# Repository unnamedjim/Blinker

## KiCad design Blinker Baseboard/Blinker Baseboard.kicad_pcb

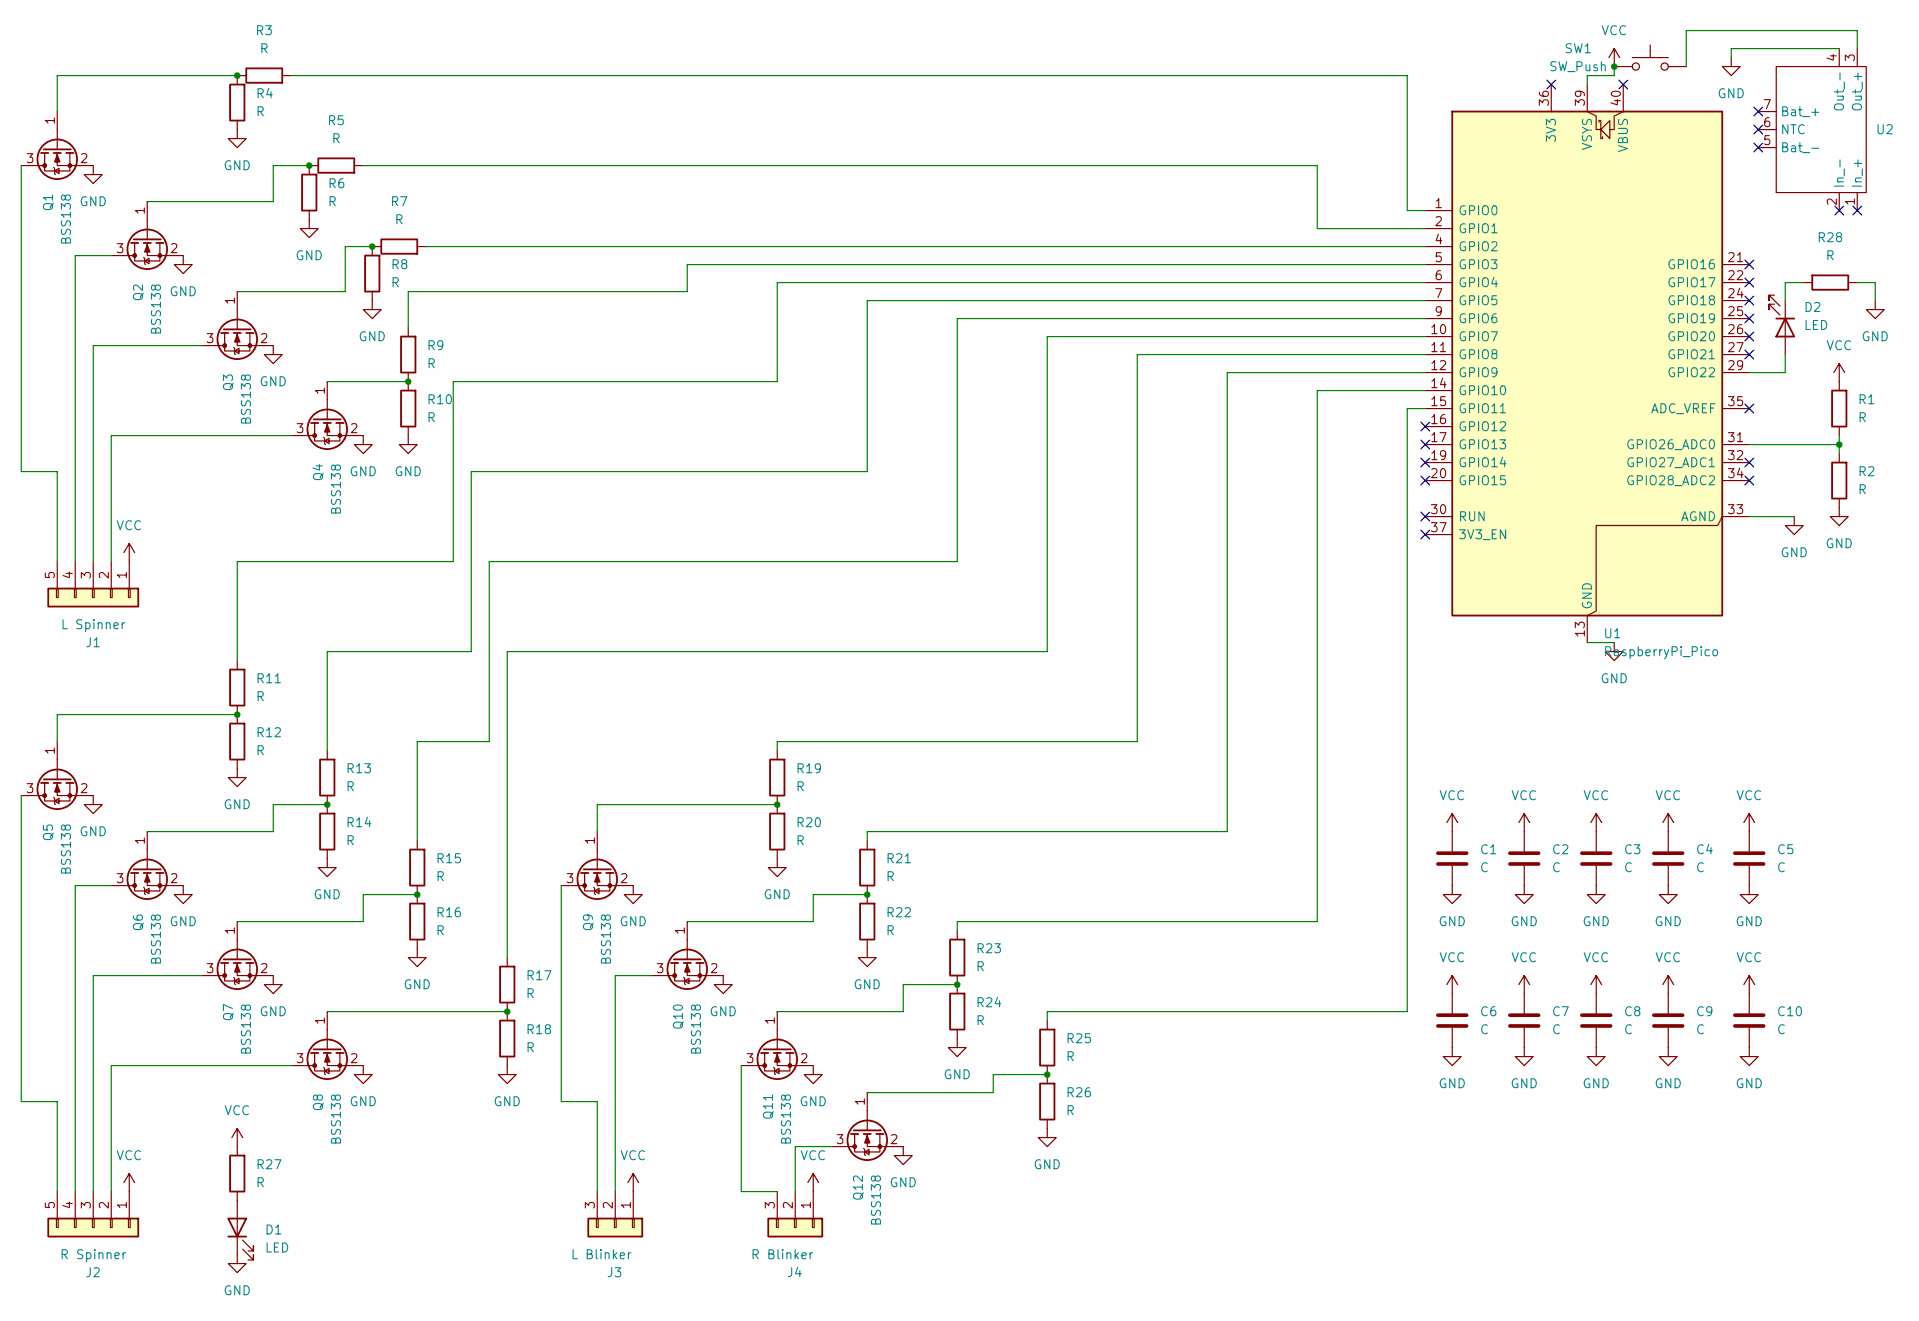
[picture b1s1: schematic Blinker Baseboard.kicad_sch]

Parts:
C1, C2, C3, C4, C5, C6, C7, C8, C9, C10: C; C_0805_2012Metric_Pad1.18x1.45mm_HandSolder
D1, D2: LED; LED_0805_2012Metric_Pad1.15x1.40mm_HandSolder
J1: L Spinner; PinHeader_1x05_P2.54mm_Vertical
J2: R Spinner; PinHeader_1x05_P2.54mm_Vertical
J3: L Blinker; PinHeader_1x03_P2.54mm_Vertical
J4: R Blinker; PinHeader_1x03_P2.54mm_Vertical
Q1, Q2, Q3, Q4, Q5, Q6, Q7, Q8, Q9, Q10, Q11, Q12: BSS138; SOT-23
R1, R2, R3, R4, R5, R6, R7, R8, R9, R10, R11, R12, R13, R14, R15, R16, R17, R18, R19, R20, R21, R22, R23, R24, R25, R26, R27, R28: R; R_0805_2012Metric_Pad1.20x1.40mm_HandSolder
SW1: SW_Push; PinHeader_1x02_P2.54mm_Vertical
U1: RaspberryPi_Pico; RaspberryPi_Pico_Common
U2: Electrokit LiPo charger

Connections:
GND: C1.2, C2.2, C3.2, C4.2, C5.2, C6.2, C7.2, C8.2, C9.2, C10.2, D1.1 (K), Q1.2 (S), Q2.2 (S), Q3.2 (S), Q4.2 (S), Q5.2 (S), Q6.2 (S), Q7.2 (S), Q8.2 (S), Q9.2 (S), Q10.2 (S), Q11.2 (S), Q12.2 (S), R2.1, R4.1, R6.1, R8.1, R10.1, R12.1, R14.1, R16.1, R18.1, R20.1, R22.1, R24.1, R26.1, R28.1, U1.3 (GND), U1.8 (GND), U1.13 (GND), U1.18 (GND), U1.23 (GND), U1.28 (GND), U1.33 (AGND), U1.38 (GND), U2.4 (Out_-)
unnamed: D1.2 (A), R27.1
unnamed: D2.2 (A), U1.29 (GPIO22)
unnamed: D2.1 (K), R28.2
unnamed: J1.2, Q4.3 (D)
unnamed: J1.3, Q3.3 (D)
unnamed: J1.4, Q2.3 (D)
unnamed: J1.5, Q1.3 (D)
unnamed: J2.2, Q8.3 (D)
unnamed: J2.3, Q7.3 (D)
unnamed: J2.4, Q6.3 (D)
unnamed: J2.5, Q5.3 (D)
unnamed: J3.2, Q10.3 (D)
unnamed: J3.3, Q9.3 (D)
unnamed: J4.2, Q12.3 (D)
unnamed: J4.3, Q11.3 (D)
unnamed: Q1.1 (G), R3.1, R4.2
unnamed: Q2.1 (G), R5.1, R6.2
unnamed: Q3.1 (G), R7.1, R8.2
unnamed: Q4.1 (G), R9.1, R10.2
unnamed: Q5.1 (G), R11.1, R12.2
unnamed: Q6.1 (G), R13.1, R14.2
unnamed: Q7.1 (G), R15.1, R16.2
unnamed: Q8.1 (G), R17.1, R18.2
unnamed: Q9.1 (G), R19.1, R20.2
unnamed: Q10.1 (G), R21.1, R22.2
unnamed: Q11.1 (G), R23.1, R24.2
unnamed: Q12.1 (G), R25.1, R26.2
unnamed: R3.2, U1.1 (GPIO0)
unnamed: R5.2, U1.2 (GPIO1)
unnamed: R7.2, U1.4 (GPIO2)
unnamed: R9.2, U1.5 (GPIO3)
unnamed: R11.2, U1.6 (GPIO4)
unnamed: R13.2, U1.7 (GPIO5)
unnamed: R15.2, U1.9 (GPIO6)
unnamed: R17.2, U1.10 (GPIO7)
unnamed: R19.2, U1.11 (GPIO8)
unnamed: R21.2, U1.12 (GPIO9)
unnamed: R23.2, U1.14 (GPIO10)
unnamed: R25.2, U1.15 (GPIO11)
unnamed: R1.1, R2.2, U1.31 (GPIO26_ADC0)
unnamed: SW1.2, U2.3 (Out_+)
VCC: C1.1, C2.1, C3.1, C4.1, C5.1, C6.1, C7.1, C8.1, C9.1, C10.1, J1.1, J2.1, J3.1, J4.1, R1.2, R27.2, SW1.1, U1.39 (VSYS)

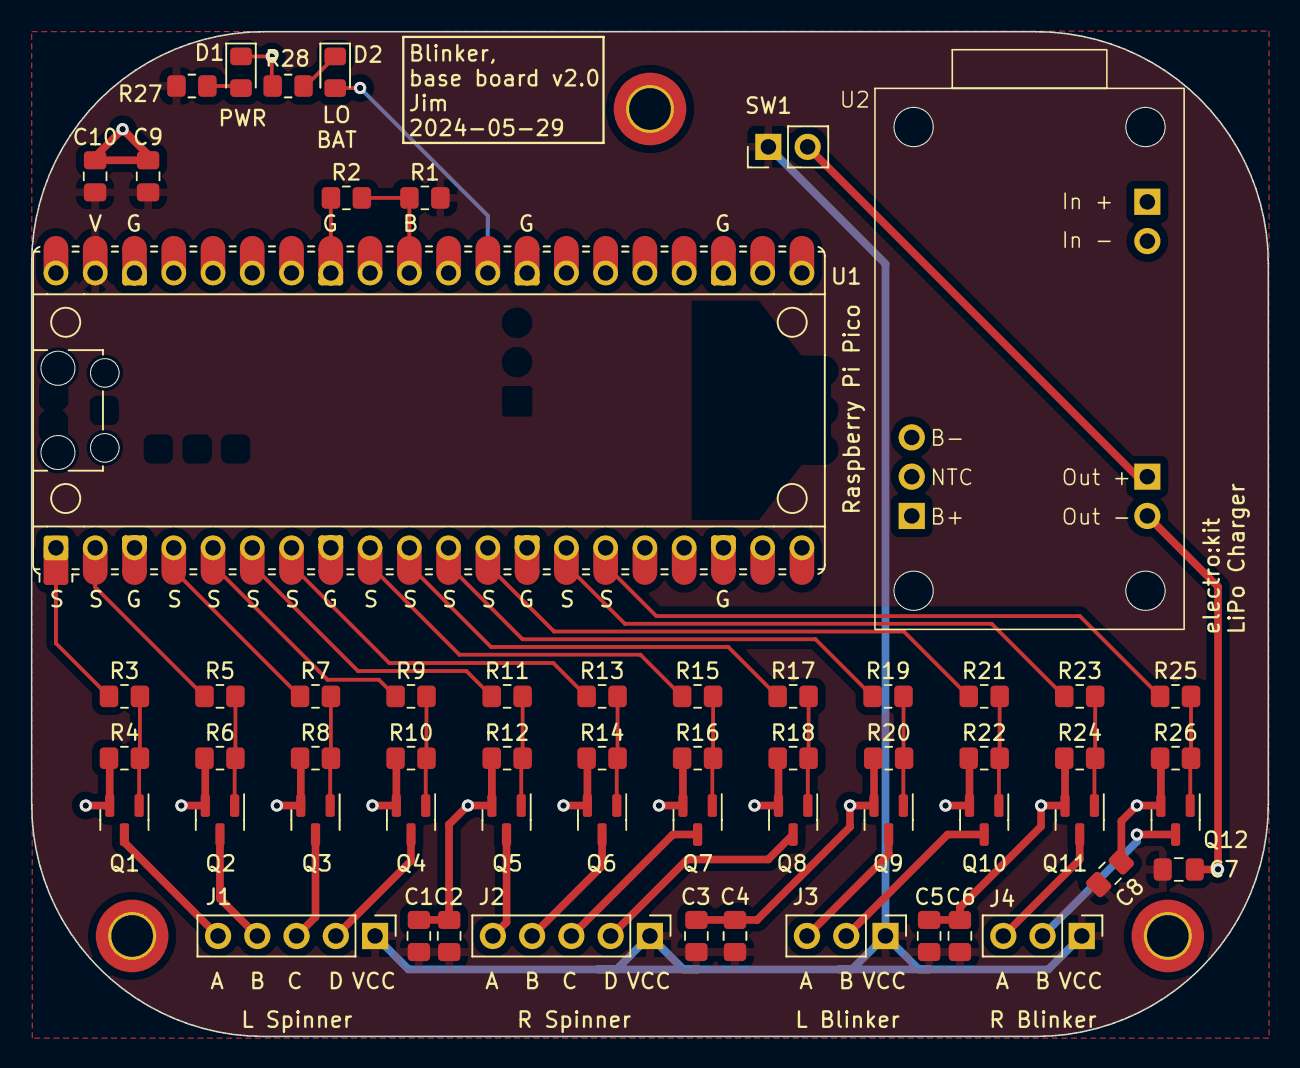
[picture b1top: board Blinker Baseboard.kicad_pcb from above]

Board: 2 copper layers, 80.0 x 65.0 mm, 59 parts (0 on the bottom side), 43 nets.

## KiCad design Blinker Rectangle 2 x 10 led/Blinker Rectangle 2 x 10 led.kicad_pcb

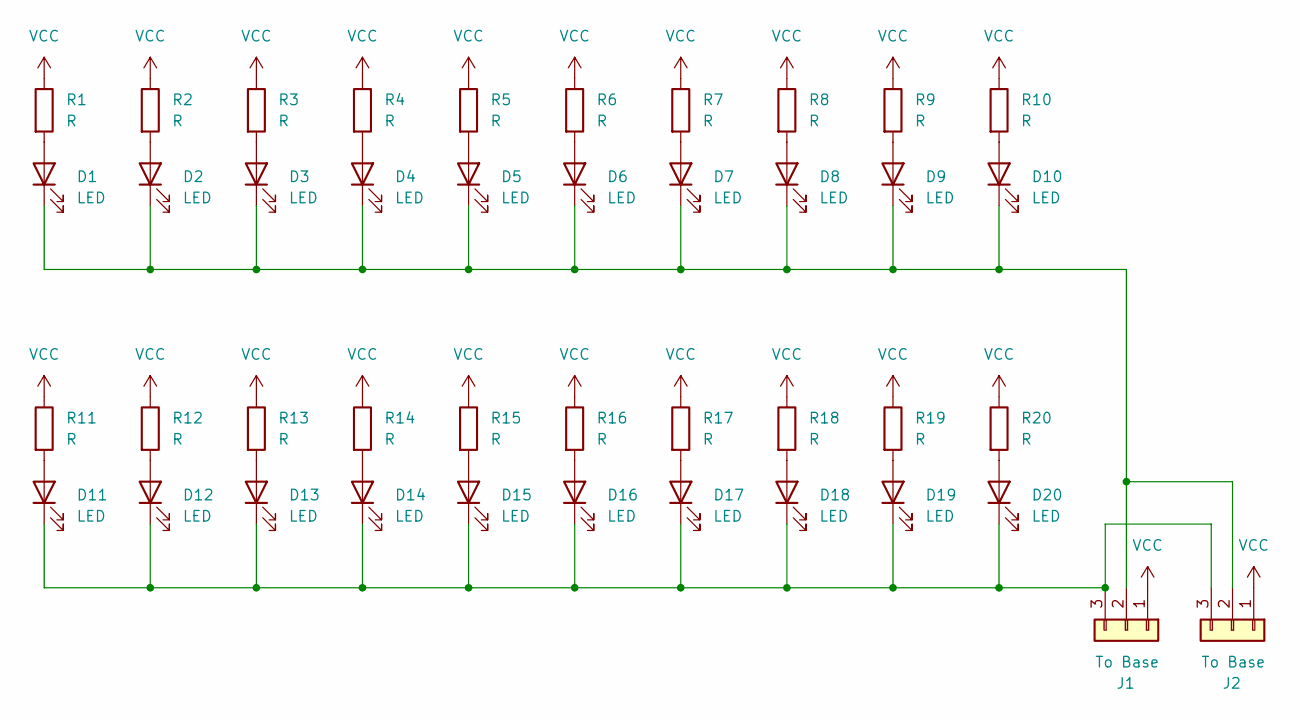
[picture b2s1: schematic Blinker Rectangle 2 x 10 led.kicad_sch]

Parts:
D1, D2, D3, D4, D5, D6, D7, D8, D9, D10, D11, D12, D13, D14, D15, D16, D17, D18, D19, D20: LED; D_1206_3216Metric_Pad1.42x1.75mm_HandSolder
J1, J2: To Base; PinHeader_1x03_P2.54mm_Vertical
R1, R2, R3, R4, R5, R6, R7, R8, R9, R10, R11, R12, R13, R14, R15, R16, R17, R18, R19, R20: R; R_1206_3216Metric_Pad1.30x1.75mm_HandSolder

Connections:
unnamed: D1.2 (A), R1.2
unnamed: D1.1 (K), D2.1 (K), D3.1 (K), D4.1 (K), D5.1 (K), D6.1 (K), D7.1 (K), D8.1 (K), D9.1 (K), D10.1 (K), J1.2, J2.2
unnamed: D2.2 (A), R2.2
unnamed: D3.2 (A), R3.2
unnamed: D4.2 (A), R4.2
unnamed: D5.2 (A), R5.2
unnamed: D6.2 (A), R6.2
unnamed: D7.2 (A), R7.2
unnamed: D8.2 (A), R8.2
unnamed: D9.2 (A), R9.2
unnamed: D10.2 (A), R10.2
unnamed: D11.2 (A), R11.2
unnamed: D11.1 (K), D12.1 (K), D13.1 (K), D14.1 (K), D15.1 (K), D16.1 (K), D17.1 (K), D18.1 (K), D19.1 (K), D20.1 (K), J1.3, J2.3
unnamed: D12.2 (A), R12.2
unnamed: D13.2 (A), R13.2
unnamed: D14.2 (A), R14.2
unnamed: D15.2 (A), R15.2
unnamed: D16.2 (A), R16.2
unnamed: D17.2 (A), R17.2
unnamed: D18.2 (A), R18.2
unnamed: D19.2 (A), R19.2
unnamed: D20.2 (A), R20.2
VCC: J1.1, J2.1, R1.1, R2.1, R3.1, R4.1, R5.1, R6.1, R7.1, R8.1, R9.1, R10.1, R11.1, R12.1, R13.1, R14.1, R15.1, R16.1, R17.1, R18.1, R19.1, R20.1

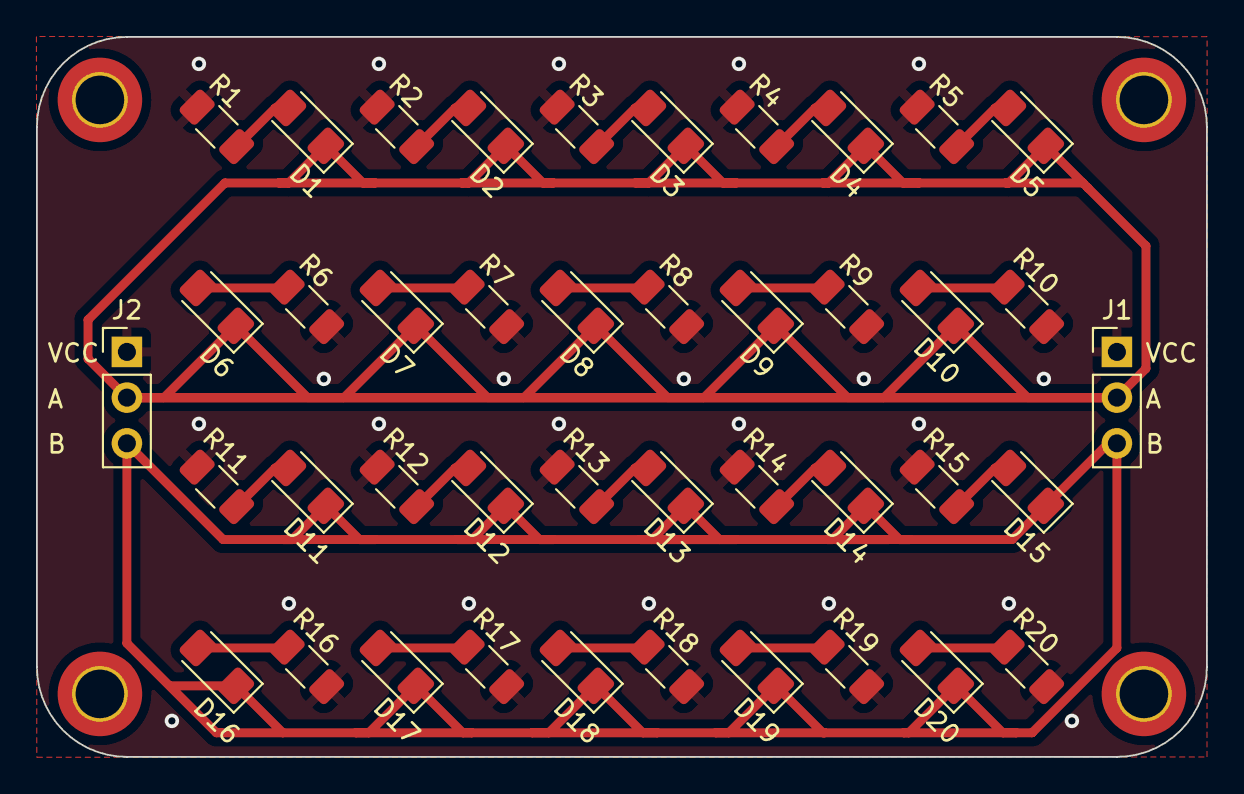
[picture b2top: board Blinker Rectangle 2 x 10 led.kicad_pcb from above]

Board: 2 copper layers, 65.0 x 40.0 mm, 42 parts (0 on the bottom side), 23 nets.

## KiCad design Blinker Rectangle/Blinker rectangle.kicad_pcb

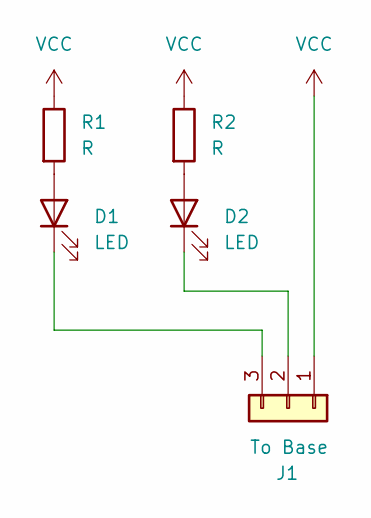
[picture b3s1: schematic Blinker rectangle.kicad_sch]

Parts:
D1, D2: LED; LED_1210_3225Metric
J1: To Base; Molex_PicoBlade_53047-0310_1x03_P1.25mm_Vertical
R1, R2: R; R_1206_3216Metric

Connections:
unnamed: D1.2 (A), R1.2
unnamed: D1.1 (K), J1.3
unnamed: D2.2 (A), R2.2
unnamed: D2.1 (K), J1.2
VCC: J1.1, R1.1, R2.1

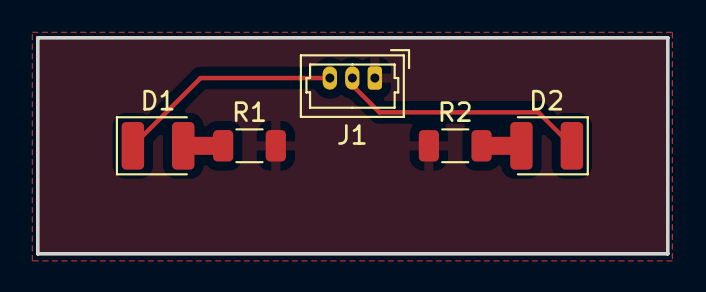
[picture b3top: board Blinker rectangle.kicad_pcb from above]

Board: 2 copper layers, 35.0 x 12.0 mm, 5 parts (0 on the bottom side), 5 nets.

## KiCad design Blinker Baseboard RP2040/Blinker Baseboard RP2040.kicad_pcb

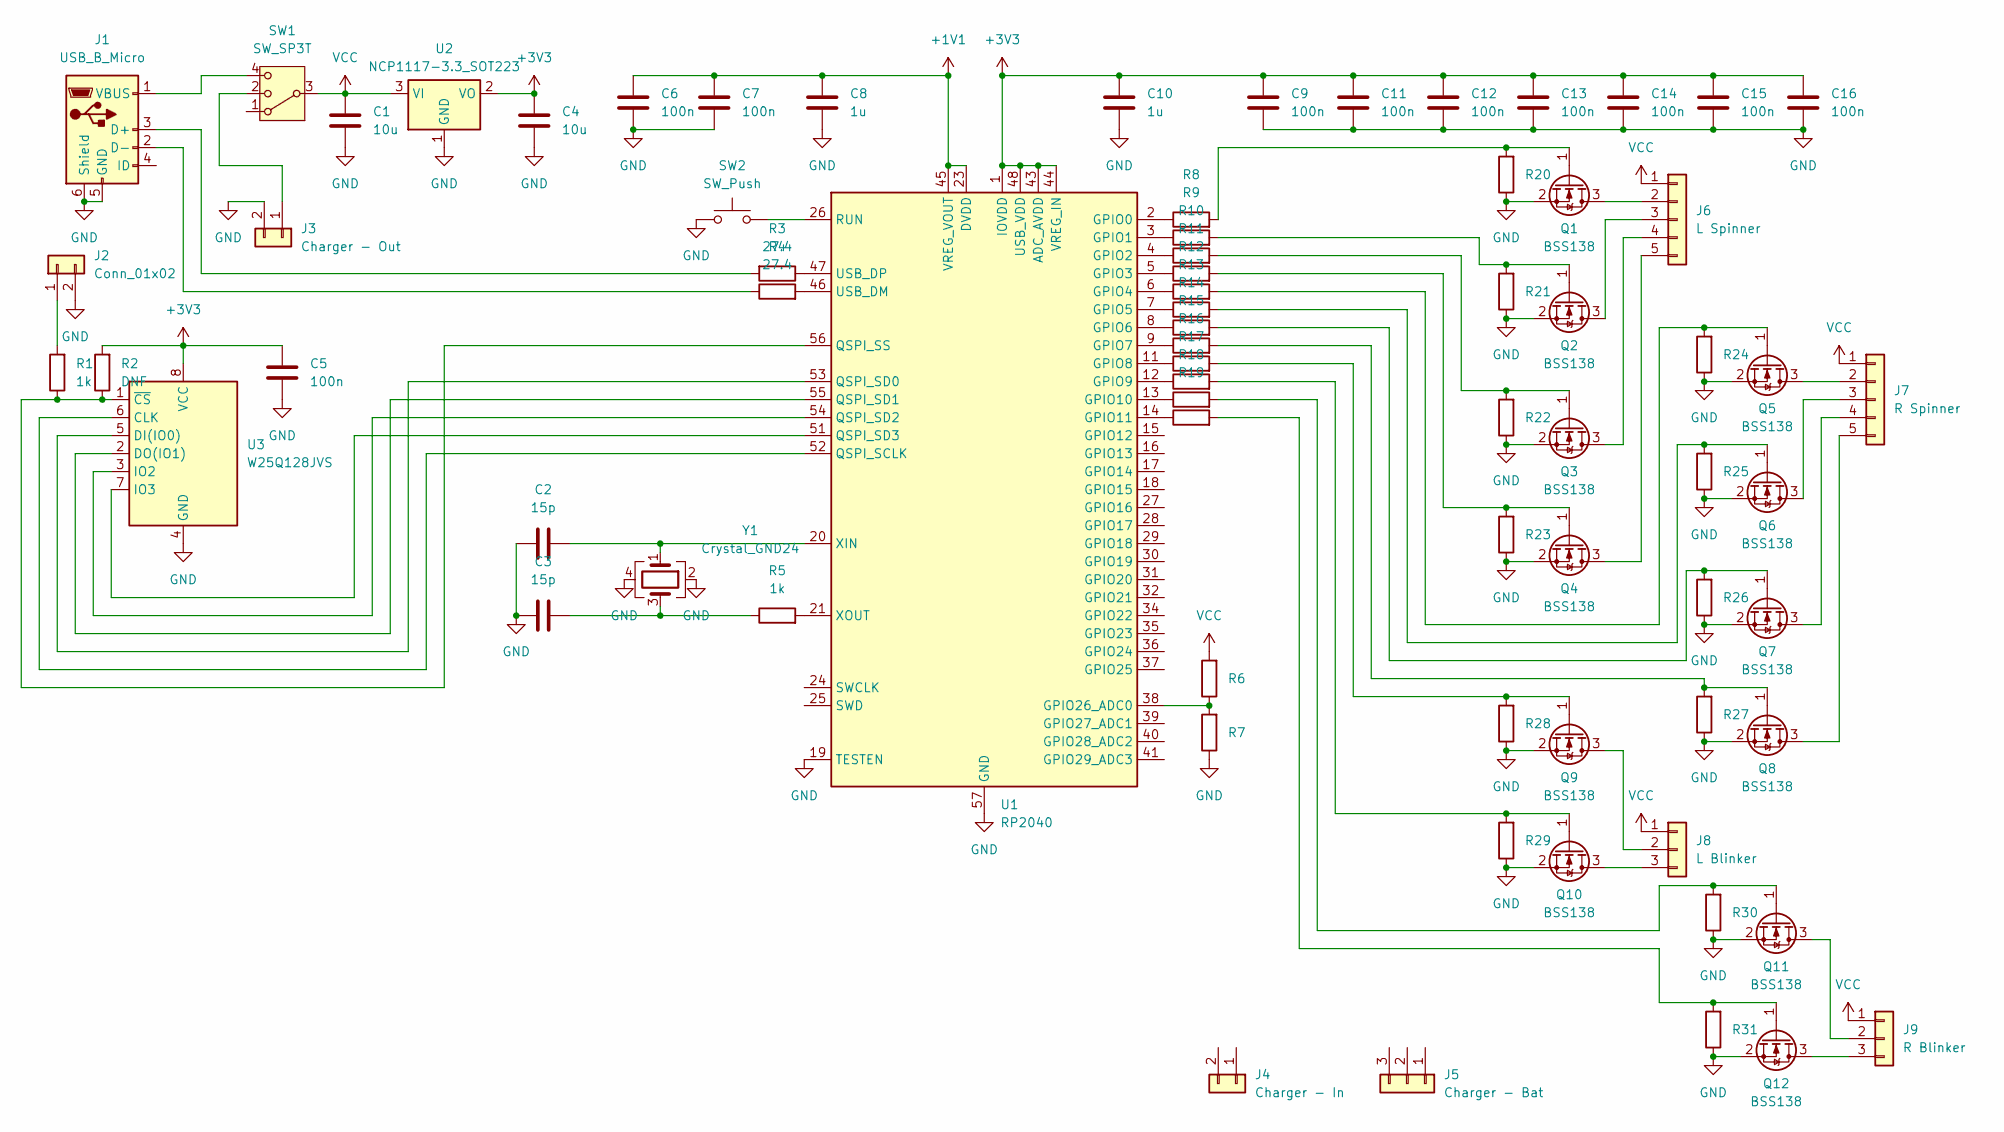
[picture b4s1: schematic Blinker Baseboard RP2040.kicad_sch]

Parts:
C1, C4: 10u; C_0805_2012Metric
C2, C3: 15p; C_0805_2012Metric
C5, C6, C7, C9, C11, C12, C13, C14, C15, C16: 100n; C_0805_2012Metric
C8, C10: 1u; C_0805_2012Metric
J1: USB_B_Micro; USB_Micro-B_Amphenol_10104110_Horizontal
J2: Conn_01x02; PinHeader_1x02_P2.54mm_Vertical
J3: Charger - Out; PinHeader_1x02_P2.54mm_Vertical
J4: Charger - In; PinHeader_1x02_P2.54mm_Vertical
J5: Charger - Bat; PinHeader_1x03_P2.54mm_Vertical
J6: L Spinner; Molex_PicoBlade_53047-0510_1x05_P1.25mm_Vertical
J7: R Spinner; Molex_PicoBlade_53047-0510_1x05_P1.25mm_Vertical
J8: L Blinker; Molex_PicoBlade_53047-0310_1x03_P1.25mm_Vertical
J9: R Blinker; Molex_PicoBlade_53047-0310_1x03_P1.25mm_Vertical
Q1, Q2, Q3, Q4, Q5, Q6, Q7, Q8, Q9, Q10, Q11, Q12: BSS138; SOT-23
R1, R5: 1k; R_0805_2012Metric
R2: DNF; R_0805_2012Metric
R3, R4: 27.4; R_0805_2012Metric
R6, R7, R8, R9, R10, R11, R12, R13, R14, R15, R16, R17, R18, R19, R20, R21, R22, R23, R24, R25, R26, R27, R28, R29, R30, R31: R_0805_2012Metric
SW1: SW_SP3T; Molex_PicoBlade_53047-0410_1x04_P1.25mm_Vertical
SW2: SW_Push; Molex_PicoBlade_53047-0210_1x02_P1.25mm_Vertical
U1: RP2040; QFN-56-1EP_7x7mm_P0.4mm_EP3.2x3.2mm
U2: NCP1117-3.3_SOT223; SOT-223-3_TabPin2
U3: W25Q128JVS; SOIC-8_5.23x5.23mm_P1.27mm
Y1: Crystal_GND24; Crystal_SMD_3225-4Pin_3.2x2.5mm

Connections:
+1V1: C6.1, C7.1, C8.1, U1.23 (DVDD), U1.45 (VREG_VOUT), U1.50 (DVDD)
+3V3: C4.1, C5.1, C9.1, C10.1, C11.1, C12.1, C13.1, C14.1, C15.1, C16.1, R2.2, U1.1 (IOVDD), U1.10 (IOVDD), U1.22 (IOVDD), U1.33 (IOVDD), U1.42 (IOVDD), U1.43 (ADC_AVDD), U1.44 (VREG_IN), U1.48 (USB_VDD), U1.49 (IOVDD), U2.2 (VO), U3.8 (VCC)
GND: C1.2, C2.1, C3.1, C4.2, C5.2, C6.2, C7.2, C8.2, C9.2, C10.2, C11.2, C12.2, C13.2, C14.2, C15.2, C16.2, J1.5 (GND), J1.6 (Shield), J2.2, J3.2, Q1.2 (S), Q2.2 (S), Q3.2 (S), Q4.2 (S), Q5.2 (S), Q6.2 (S), Q7.2 (S), Q8.2 (S), Q9.2 (S), Q10.2 (S), Q11.2 (S), Q12.2 (S), R7.1, R20.1, R21.1, R22.1, R23.1, R24.1, R25.1, R26.1, R27.1, R28.1, R29.1, R30.1, R31.1, SW2.1, U1.19 (TESTEN), U1.57 (GND), U2.1 (GND), U3.4 (GND), Y1.2, Y1.4
unnamed: C3.2, R5.1, Y1.3
unnamed: J1.3 (D+), R3.2
unnamed: J1.2 (D-), R4.1
unnamed: J1.1 (VBUS), SW1.4
unnamed: J2.1, R1.2
unnamed: J3.1, SW1.2
unnamed: J6.2, Q1.3 (D)
unnamed: J6.3, Q2.3 (D)
unnamed: J6.4, Q3.3 (D)
unnamed: J6.5, Q4.3 (D)
unnamed: J7.2, Q5.3 (D)
unnamed: J7.3, Q6.3 (D)
unnamed: J7.4, Q7.3 (D)
unnamed: J7.5, Q8.3 (D)
unnamed: J8.2, Q9.3 (D)
unnamed: J8.3, Q10.3 (D)
unnamed: J9.2, Q11.3 (D)
unnamed: J9.3, Q12.3 (D)
unnamed: Q1.1 (G), R8.2, R20.2
unnamed: Q2.1 (G), R9.2, R21.2
unnamed: Q3.1 (G), R10.2, R22.2
unnamed: Q4.1 (G), R11.2, R23.2
unnamed: Q5.1 (G), R12.2, R24.2
unnamed: Q6.1 (G), R13.2, R25.2
unnamed: Q7.1 (G), R14.2, R26.2
unnamed: Q8.1 (G), R15.2, R27.2
unnamed: Q9.1 (G), R16.2, R28.2
unnamed: Q10.1 (G), R17.2, R29.2
unnamed: Q11.1 (G), R18.2, R30.2
unnamed: Q12.1 (G), R19.2, R31.2
unnamed: R8.1, U1.2 (GPIO0)
unnamed: R9.1, U1.3 (GPIO1)
unnamed: R10.1, U1.4 (GPIO2)
unnamed: R11.1, U1.5 (GPIO3)
unnamed: R12.1, U1.6 (GPIO4)
unnamed: R13.1, U1.7 (GPIO5)
unnamed: R14.1, U1.8 (GPIO6)
unnamed: R15.1, U1.9 (GPIO7)
unnamed: R16.1, U1.11 (GPIO8)
unnamed: R17.1, U1.12 (GPIO9)
unnamed: R18.1, U1.13 (GPIO10)
unnamed: R19.1, U1.14 (GPIO11)
unnamed: R6.1, R7.2, U1.38 (GPIO26_ADC0)
unnamed: U1.52 (QSPI_SCLK), U3.6 (CLK)
unnamed: U1.53 (QSPI_SD0), U3.5 (DI(IO0))
unnamed: U1.55 (QSPI_SD1), U3.2 (DO(IO1))
unnamed: U1.54 (QSPI_SD2), U3.3 (IO2)
unnamed: U1.51 (QSPI_SD3), U3.7 (IO3)
unnamed: R1.1, R2.1, U1.56 (QSPI_SS), U3.1 (~CS)
unnamed: SW2.2, U1.26 (RUN)
unnamed: R4.2, U1.46 (USB_DM)
unnamed: R3.1, U1.47 (USB_DP)
unnamed: C2.2, U1.20 (XIN), Y1.1
unnamed: R5.2, U1.21 (XOUT)
VCC: C1.1, J6.1, J7.1, J8.1, J9.1, R6.2, SW1.3, U2.3 (VI)

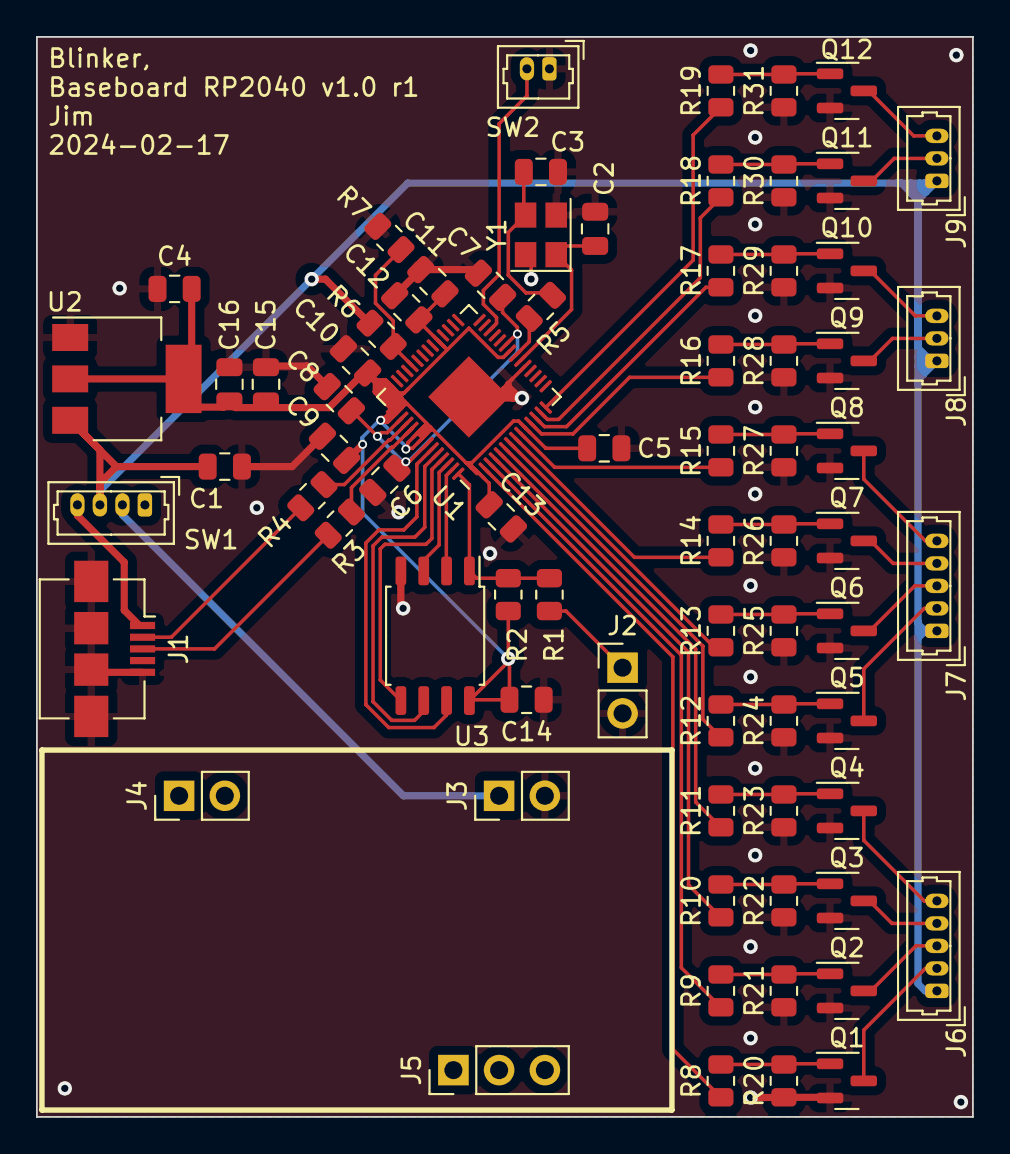
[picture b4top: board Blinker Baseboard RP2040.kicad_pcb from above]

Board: 2 copper layers, 52.0 x 60.0 mm, 74 parts (0 on the bottom side), 58 nets.

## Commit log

2024-02-13 v 1.0
2024-03-14 Added code
    First working firmware.
2024-05-28 Added Rectangle 2 x 10
2024-05-29 Baseboard rework
    R2 became v2.
2024-06-27 Fix clearances
2024-06-27 Fixed more clearances
